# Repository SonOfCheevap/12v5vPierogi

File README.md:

# 12v5vPierogi
A 12v to 5v Convertor using the TPS54302 from TI

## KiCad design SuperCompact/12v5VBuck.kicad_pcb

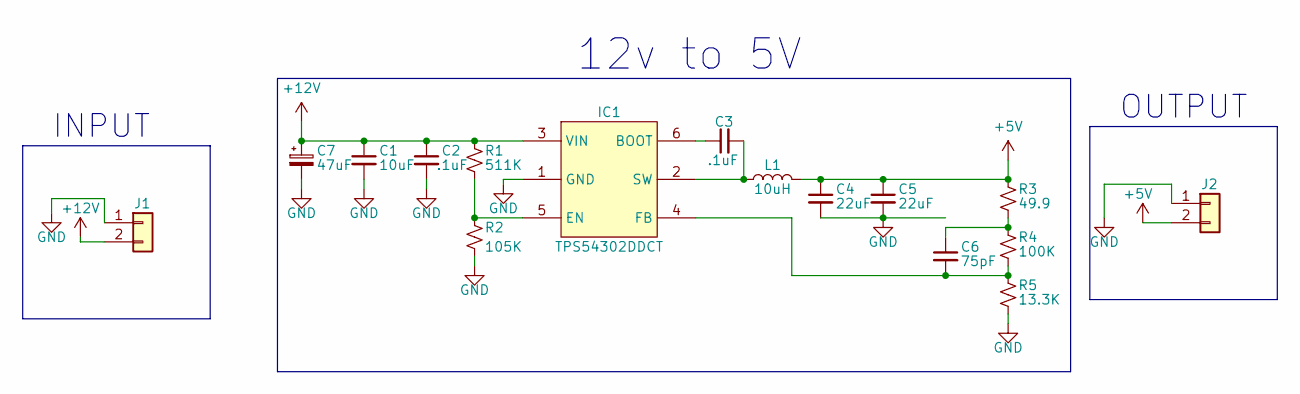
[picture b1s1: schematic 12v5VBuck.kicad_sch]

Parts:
C1: 10uF; C_0805_2012Metric
C2, C3: .1uF; C_0805_2012Metric
C4, C5: 22uF; C_0805_2012Metric
C6: 75pF; C_0805_2012Metric
C7: 47uF; CAPPM3216X180N
IC1: TPS54302DDCT; SOT95P280X110-6N; Manufacturer_Part_Number TPS54302DDCT; Mouser Part Number 595-TPS54302DDCT
J1, J2: Conn_01x02; CONN_1984617_PXC
L1: 10uH; L_Abracon_ASPI-0630LR
R1: 511K; R_0805_2012Metric
R2: 105K; R_0805_2012Metric
R3: 49.9; R_0805_2012Metric
R4: 100K; R_0805_2012Metric
R5: 13.3K; R_0805_2012Metric

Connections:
+5V: C4.1, C5.1, J2.2, L1.2, R3.1
+12V: C1.1, C2.1, C7.1, IC1.3 (VIN), J1.2, R1.1
GND: C1.2, C2.2, C4.2, C5.2, C7.2, IC1.1 (GND), J1.1, J2.1, R2.2, R5.2
unnamed: C6.1, R3.2, R4.1
unnamed: C3.1, IC1.6 (BOOT)
unnamed: IC1.5 (EN), R1.2, R2.1
unnamed: C6.2, IC1.4 (FB), R4.2, R5.1
unnamed: C3.2, IC1.2 (SW), L1.1

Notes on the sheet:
12v to 5V
INPUT
OUTPUT

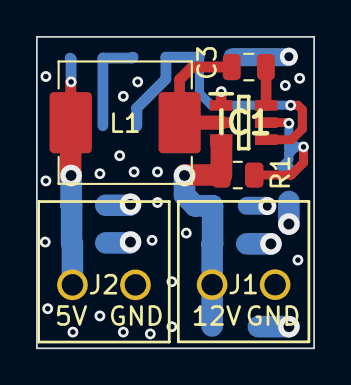
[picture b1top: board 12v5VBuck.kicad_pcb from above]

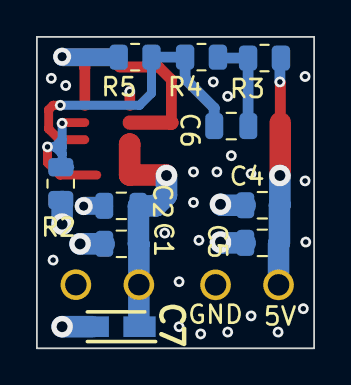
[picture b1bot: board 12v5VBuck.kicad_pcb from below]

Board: 4 copper layers, 15.4 x 17.3 mm, 16 parts (10 on the bottom side), 8 nets.

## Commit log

2023-12-07 Initial commit w/ schematic
2023-12-07 updated schematic
2023-12-08 Added first buck convertor
2023-12-08 Added a few more gnd vias
2023-12-08 Added a mounting hole
2023-12-08 Minor changes to traces
2023-12-08 Changed capacitor type for 47uF capacitor
2023-12-08 Changed resistor to front
2023-12-08 Added additional version that is extremely compact
2023-12-08 Updated schematic with link to new capacitor
2023-12-12 Added bypass capacitor to input
2023-12-12 Added labels
2023-12-12 Updated footprint labels
2024-06-07 Create LICENSE
